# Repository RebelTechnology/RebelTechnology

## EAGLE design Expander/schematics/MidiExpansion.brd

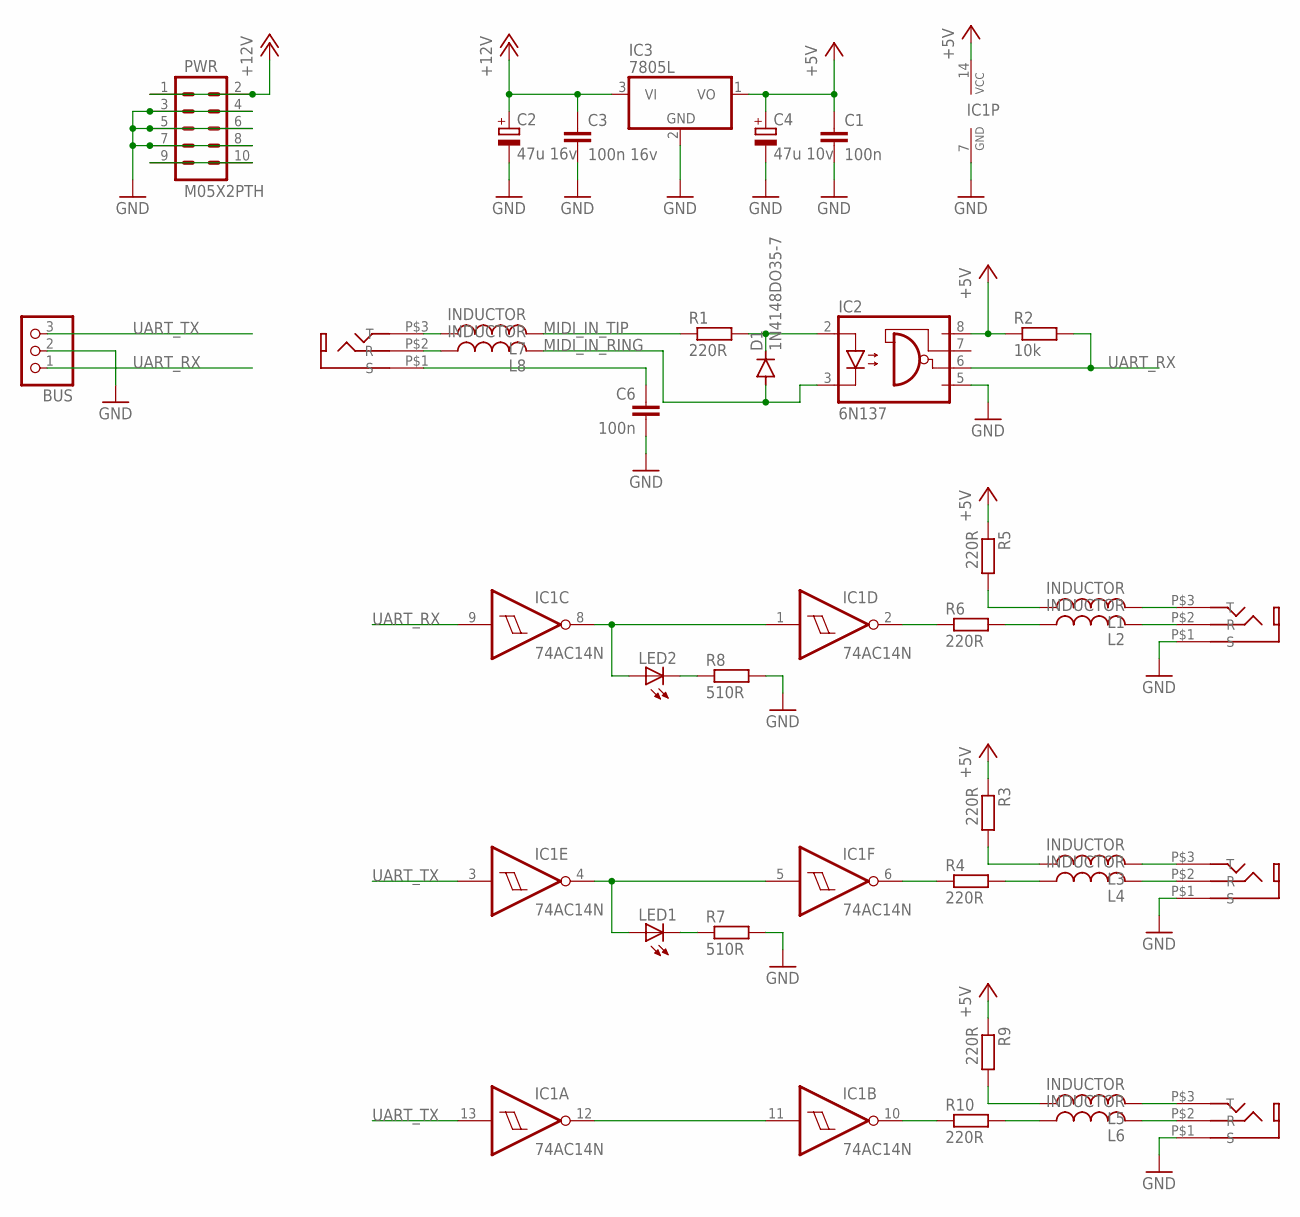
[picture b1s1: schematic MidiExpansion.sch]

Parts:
BUS: CON-JST-1X03PH-TH; JST-B3B-PH-KL
C1, C6: 100n; C050-024X044
C2: 47u 16v; E5-6
C3: 100n 16v; C050-024X044
C4: 47u 10v; E5-6
D1: 1N4148DO35-7; DO35-7
IC1: 74AC14N; DIL14
IC2: 6N137; DIL08
IC3: 7805L; TO92
L1, L2, L3, L4, L5, L6, L7, L8: INDUCTOR; 0603
LED1, LED2: LED3MM
MIDI_IN: THONKICONN_STEREO
MIDI_OUT, MIDI_OUT1: THONKICONN_STEREO
MIDI_THRU: THONKICONN_STEREO
PWR: M05X2PTH; AVR_ICSP
R1, R3, R4, R5, R6, R9, R10: 220R; 0204/7
R2: 10k; 0204/7
R7, R8: 510R; 0204/7

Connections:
+5V: C1.1, C4.+, IC1.14 (VCC), IC2.8 (VCC), IC3.1 (VO), R2.1, R3.1, R5.1, R9.1
+12V: C2.+, C3.1, IC3.3 (VI), PWR.1, PWR.2
GND: BUS.2, C1.2, C2.-, C3.2, C4.-, C6.2, IC1.7 (GND), IC2.5 (GND), IC3.2 (GND), MIDI_OUT.P$1 (S), MIDI_OUT1.P$1 (S), MIDI_THRU.P$1 (S), PWR.3, PWR.4, PWR.5, PWR.6, PWR.7, PWR.8, R7.2, R8.2
MIDI_IN_RING: D1.A, IC2.3 (C), L8.2
MIDI_IN_TIP: L7.2, R1.1
MIDI_OUT_TIP: L3.1, R3.2
MIDI_OUT_TIP1: L1.1, R5.2
MIDI_OUT_TIP2: L5.1, R9.2
unnamed: D1.C, IC2.2 (A), R1.2
unnamed: C6.1, MIDI_IN.P$1 (S)
unnamed: L2.2, MIDI_THRU.P$2 (R)
unnamed: IC1.6 (O), R4.1
unnamed: L4.2, MIDI_OUT.P$2 (R)
unnamed: IC1.4 (O), IC1.5 (I), LED1.A
unnamed: PWR.9, PWR.10
unnamed: IC1.2 (O), R6.1
unnamed: IC1.11 (I), IC1.12 (O)
unnamed: IC1.1 (I), IC1.8 (O), LED2.A
unnamed: L6.2, MIDI_OUT1.P$2 (R)
unnamed: IC1.10 (O), R10.1
unnamed: LED1.K (C), R7.1
unnamed: LED2.K (C), R8.1
unnamed: L1.2, MIDI_THRU.P$3 (T)
unnamed: L2.1, R6.2
unnamed: L3.2, MIDI_OUT.P$3 (T)
unnamed: L4.1, R4.2
unnamed: L5.2, MIDI_OUT1.P$3 (T)
unnamed: L6.1, R10.2
unnamed: L7.1, MIDI_IN.P$3 (T)
unnamed: L8.1, MIDI_IN.P$2 (R)
UART_RX: BUS.1, IC1.9 (I), IC2.6 (VO), R2.2
UART_TX: BUS.3, IC1.3 (I), IC1.13 (I)

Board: 2 copper layers, 35 parts (0 on the bottom side), 32 nets, no tracks yet.

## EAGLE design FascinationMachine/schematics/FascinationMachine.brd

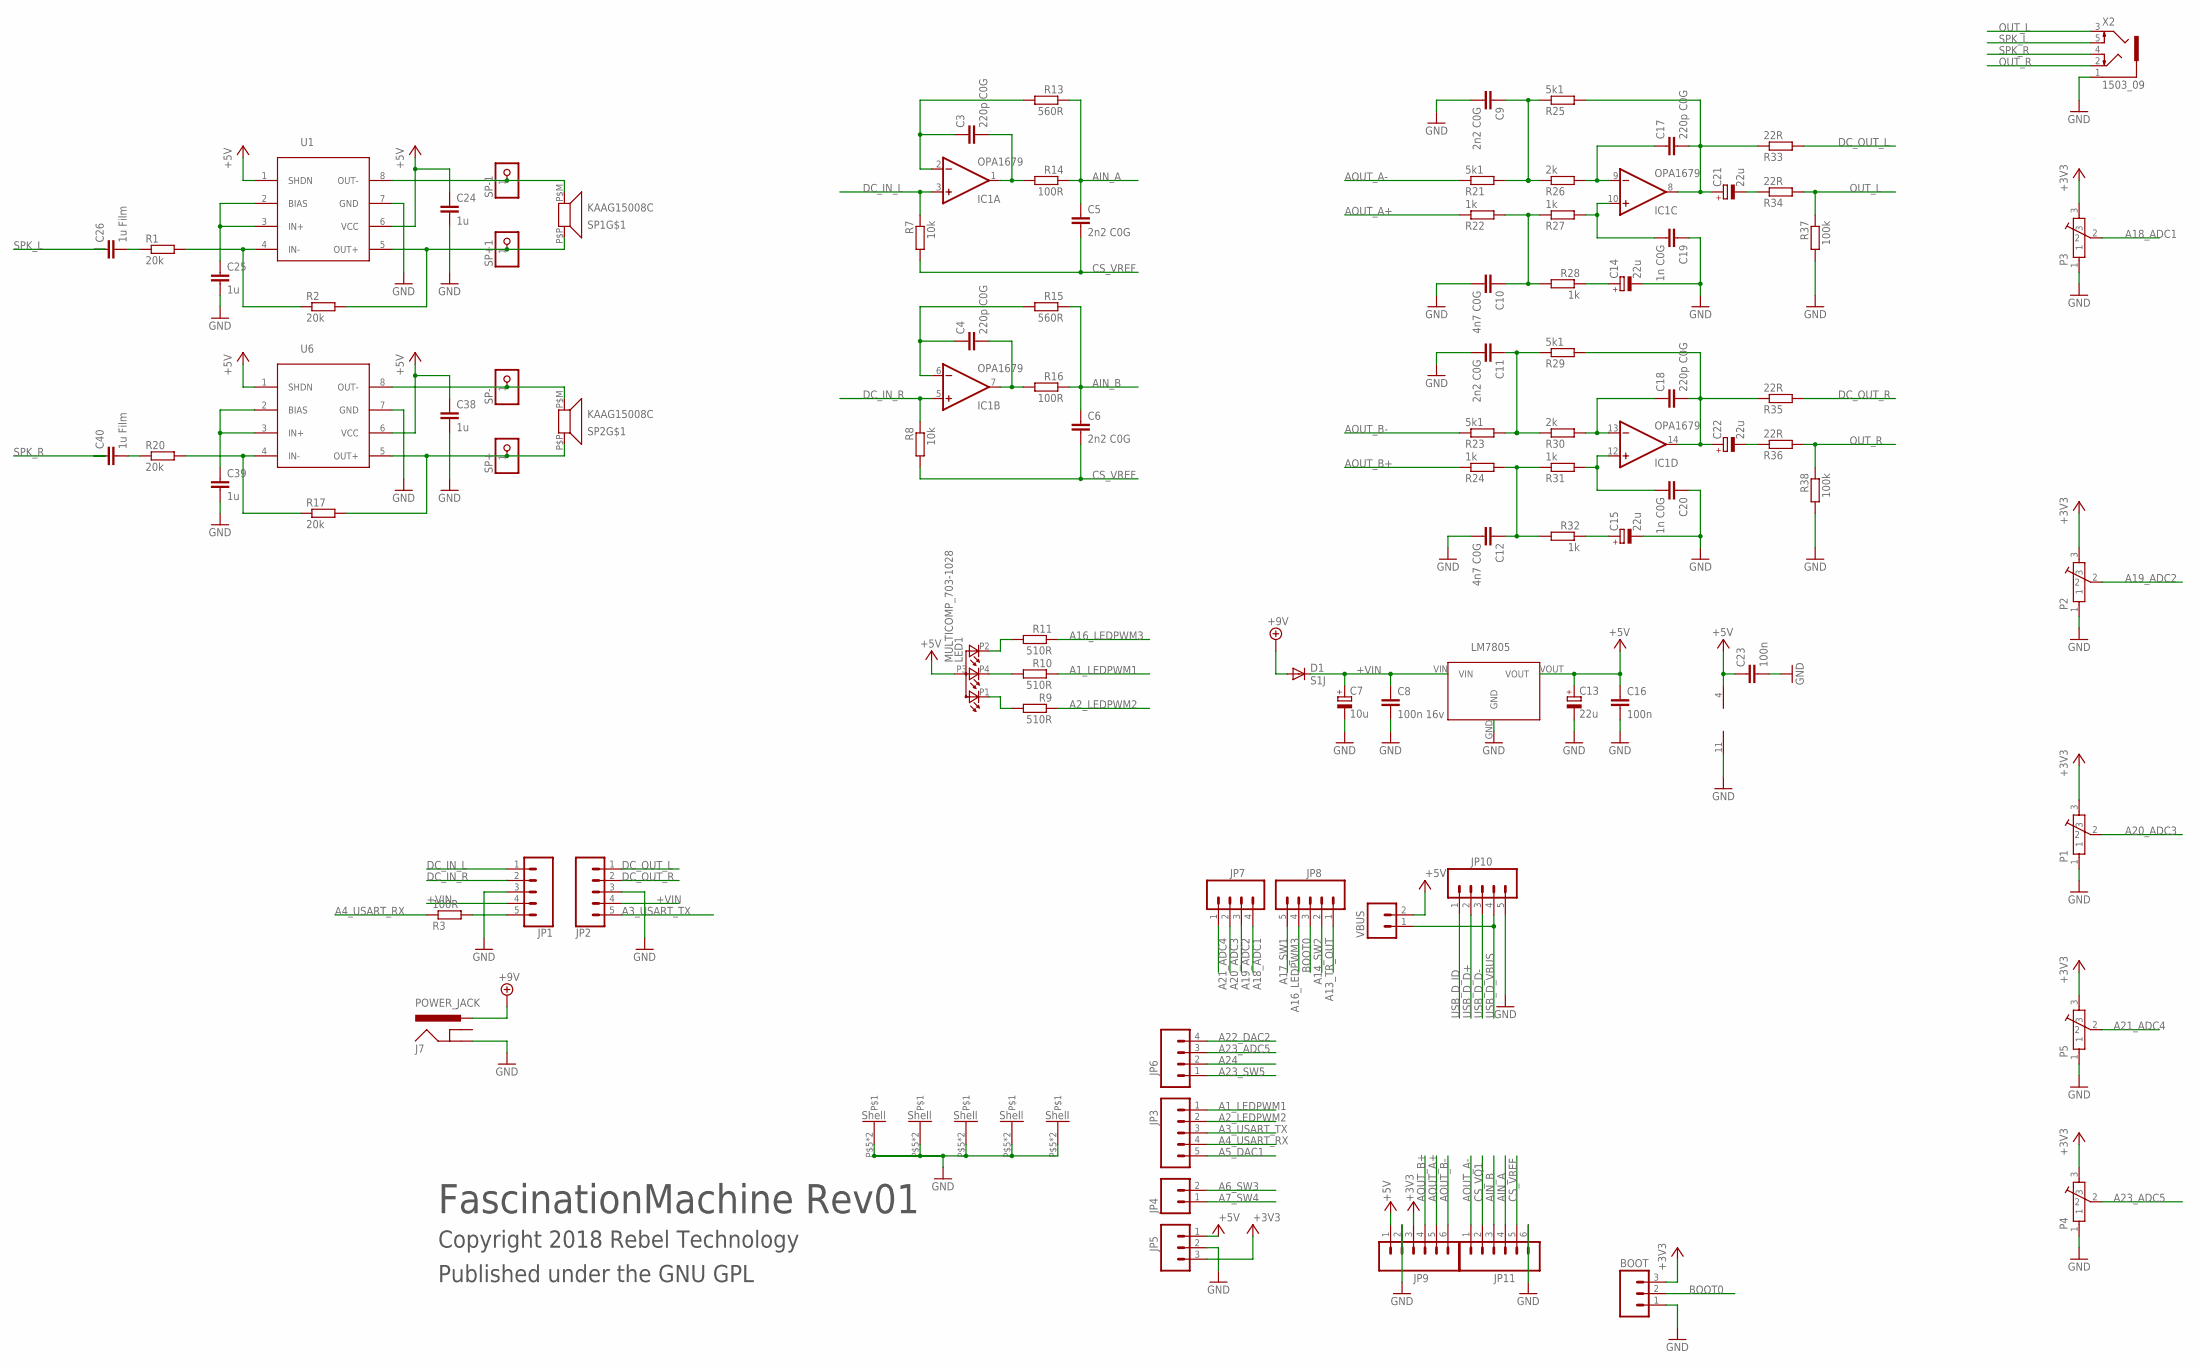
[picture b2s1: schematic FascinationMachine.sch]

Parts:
BOOT: M03PTH; 1X03
C3, C4, C17, C18: 220p C0G; C0603
C5, C6, C9, C11: 2n2 C0G; C0603
C7: 10u; 153CLV-0405
C8: 100n 16v; C0603
C10, C12: 4n7 C0G; C0603
C13, C14, C15, C21, C22: 22u; CPOL-5
C16, C23: 100n; C0603
C19, C20: 1n C0G; C0603
C24, C25, C38, C39: 1u; C0603
C26, C40: 1u Film; C1210
D1: S1J; SMA-DIODE
IC1: OPA1679; SO14
J7: POWER_JACK; DC_JACK_SLOT
JP1, JP2: CONN_05JST-VERT; JST-5-PTH-VERT
JP3, JP8, JP10: M05PTH; 1X05
JP4: M02PTH; 1X02
JP5: M03PTH; 1X03
JP6, JP7: M04PTH; 1X04
JP9, JP11: M06SIP; 1X06
LED1: MULTICOMP_703-1028; RGB-LED-703-1028
P1, P2, P3, P4, P5: POT-ALPS-RK09L1140
R1, R2, R17, R20: 20k; 0603
R3, R14, R16: 100R; 0603
R7, R8: 10k; 0603
R9, R10, R11: 510R; 0603
R13, R15: 560R; 0603
R21, R23, R25, R29: 5k1; 0603
R22, R24, R27, R28, R31, R32: 1k; 0603
R26, R30: 2k; 0603
R33, R34, R35, R36: 22R; 0603
R37, R38: 100k; 0603
SP1, SP2: KAAG15008C
SP+, SP+1: PINHD-1X1; 1X01
SP-, SP-1: PINHD-1X1; 1X01
U1, U6: MAX9716; UMAX8-THERMAL
U2: LM7805; REG_S9V11F5
VBUS: M02PTH; 1X02
X2: 1503_09

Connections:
+3V3: BOOT.3, JP5.3, JP9.3, P1.3, P2.3, P3.3, P4.3, P5.3
+5V: C13.+, C16.1, C23.1, C24.1, C38.1, IC1.4 (V+), JP5.1, JP9.1, LED1.P3 (A), U1.1 (SHDN), U1.6 (VCC), U2.VOUT, U6.1 (SHDN), U6.6 (VCC), VBUS.2
+9V: D1.A, J7.PWR
+VIN: C7.+, C8.1, D1.C, JP1.4, JP2.4, U2.VIN
A1_LEDPWM1: JP3.1, R10.1
A2_LEDPWM2: JP3.2, R9.1
A3_USART_TX: JP2.5, JP3.3
A4_USART_RX: JP3.4, R3.1
A5_DAC1: JP3.5
A6_SW3: JP4.2
A7_SW4: JP4.1
A13_TR_OUT: JP8.1
A14_SW2: JP8.2
A16_LEDPWM3: JP8.4, R11.1
A17_SW1: JP8.5
A18_ADC1: JP7.4, P3.2
A19_ADC2: JP7.3, P2.2
A20_ADC3: JP7.2, P1.2
A21_ADC4: JP7.1, P5.2
A22_DAC2: JP6.4
A23_ADC5: JP6.3, P4.2
A23_SW5: JP6.1
A24: JP6.2
AIN_A: C5.1, JP11.4, R13.1, R14.1
AIN_B: C6.1, JP11.3, R15.1, R16.1
AOUT_A+: JP9.5, R22.1
AOUT_A-: JP11.1, R21.1
AOUT_B+: JP9.4, R24.1
AOUT_B-: JP9.6, R23.1
BOOT0: BOOT.2, JP8.3
CS_VQ1: JP11.2
CS_VREF: C5.2, C6.2, JP11.5, R7.2, R8.2
DC_IN_L: IC1.3 (+IN), JP1.1, R7.1
DC_IN_R: IC1.5 (+IN), JP1.2, R8.1
DC_OUT_L: JP2.1, R33.2
DC_OUT_R: JP2.2, R35.2
GND: BOOT.1, C7.-, C8.2, C9.2, C10.2, C11.2, C12.2, C13.-, C14.-, C15.-, C16.2, C19.1, C20.1, C23.2, C24.2, C25.2, C38.2, C39.2, IC1.11 (V-), J7.GND, JP1.3, JP2.3, JP5.2, JP9.2, JP10.5, JP11.6, P1.1, P1.P$5, P1.P$6, P2.1, P2.P$5, P2.P$6, P3.1, P3.P$5, P3.P$6, P4.1, P4.P$5, P4.P$6, P5.1, P5.P$5, P5.P$6, R37.2, R38.2, U1.7 (GND), U2.GND, U6.7 (GND), X2.1
unnamed: JP1.5, R3.2
unnamed: R2.2, SP1.P$P (1), SP+1.1, U1.5 (OUT+)
unnamed: C3.1, IC1.2 (-IN), R13.2
unnamed: C4.2, IC1.7 (OUT), R16.2
unnamed: C4.1, IC1.6 (-IN), R15.2
unnamed: C3.2, IC1.1 (OUT), R14.2
unnamed: C17.1, IC1.9 (-IN), R26.2
unnamed: C15.+, R32.1
unnamed: C21.-, R34.1
unnamed: C14.+, R28.1
unnamed: C19.2, IC1.10 (+IN), R27.2
unnamed: C18.2, C22.+, IC1.14 (OUT), R29.2, R35.1
unnamed: C22.-, R36.1
unnamed: LED1.P2 (CGREEN), R11.2
unnamed: C10.1, R22.2, R27.1, R28.2
unnamed: LED1.P1 (CRED), R9.2
unnamed: LED1.P4 (CBLUE), R10.2
unnamed: SP1.P$M (2), SP-1.1, U1.8 (OUT-)
unnamed: C25.1, U1.2 (BIAS), U1.3 (IN+)
unnamed: R1.2, R2.1, U1.4 (IN-)
unnamed: C26.2, R1.1
unnamed: C11.1, R23.2, R29.1, R30.1
unnamed: C18.1, IC1.13 (-IN), R30.2
unnamed: C20.2, IC1.12 (+IN), R31.2
unnamed: C12.1, R24.2, R31.1, R32.2
unnamed: C17.2, C21.+, IC1.8 (OUT), R25.2, R33.1
unnamed: C9.1, R21.2, R25.1, R26.1
unnamed: R17.2, SP2.P$P (1), SP+.1, U6.5 (OUT+)
unnamed: SP2.P$M (2), SP-.1, U6.8 (OUT-)
unnamed: C39.1, U6.2 (BIAS), U6.3 (IN+)
unnamed: R17.1, R20.2, U6.4 (IN-)
unnamed: C40.2, R20.1
OUT_L: R34.2, R37.1, X2.3
OUT_R: R36.2, R38.1, X2.2
SPK_L: C26.1, X2.5
SPK_R: C40.1, X2.4
USB_D_D+: JP10.2
USB_D_D-: JP10.3
USB_D_ID: JP10.1
USB_D_VBUS: JP10.4, VBUS.1

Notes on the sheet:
FascinationMachine Rev01
Copyright 2018 Rebel Technology
Published under the GNU GPL

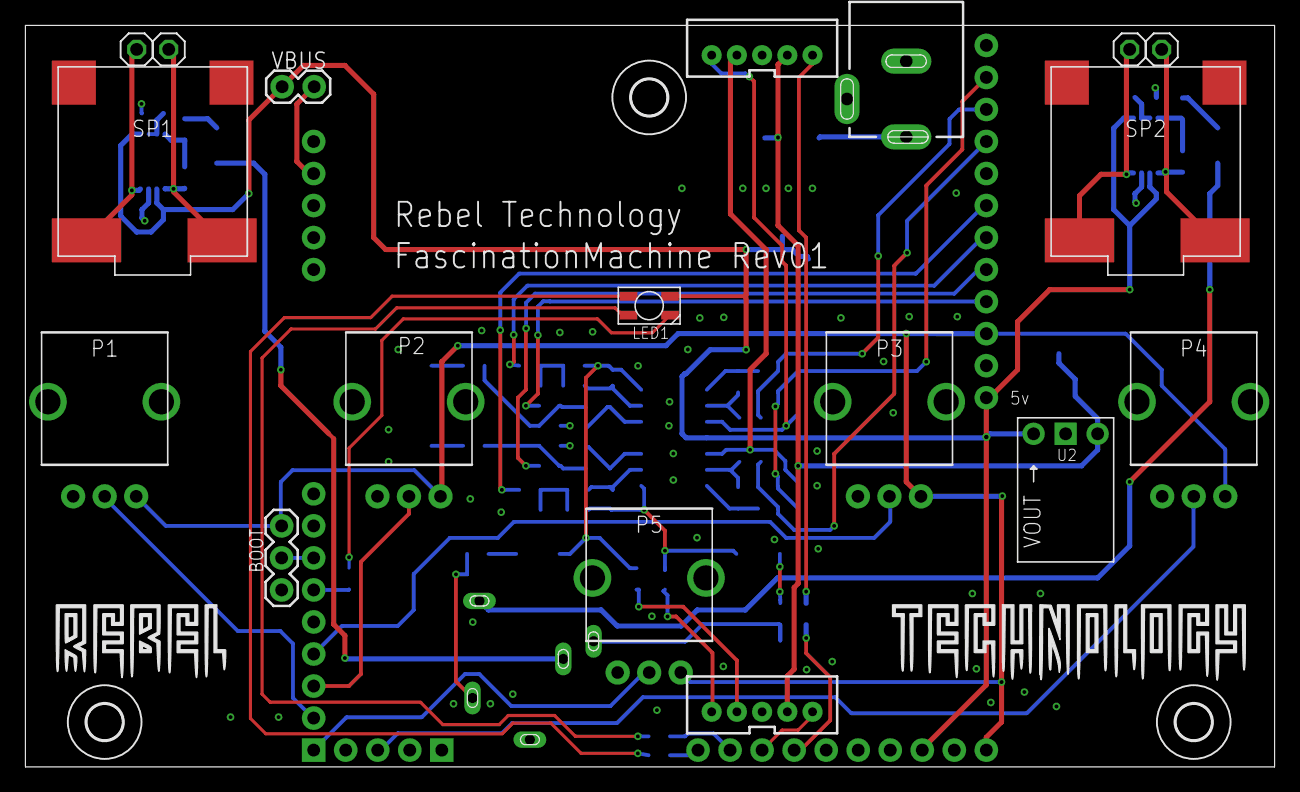
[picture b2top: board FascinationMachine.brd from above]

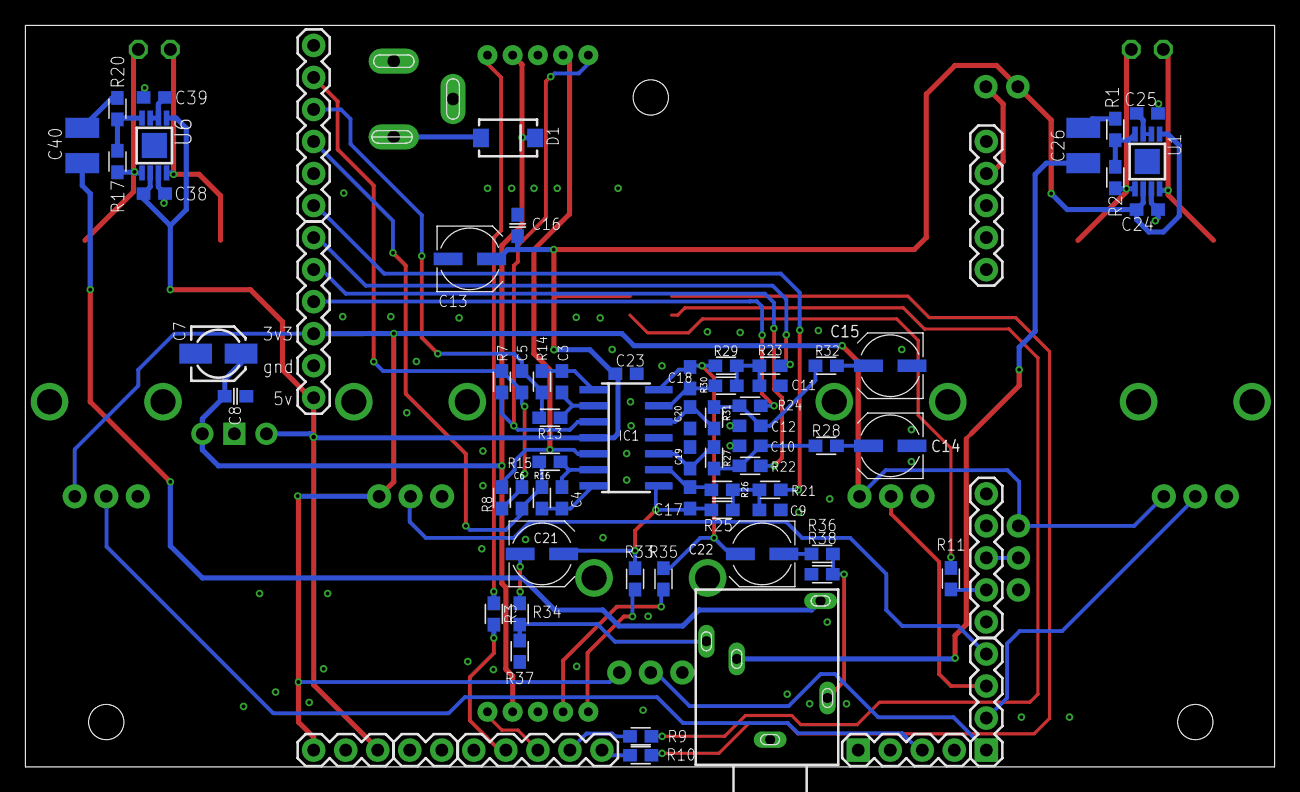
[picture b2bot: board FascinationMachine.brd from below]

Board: 2 copper layers, 99.1 x 58.8 mm, 94 parts (73 on the bottom side), 64 nets.

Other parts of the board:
U$1, U$2, U$3: 2,8

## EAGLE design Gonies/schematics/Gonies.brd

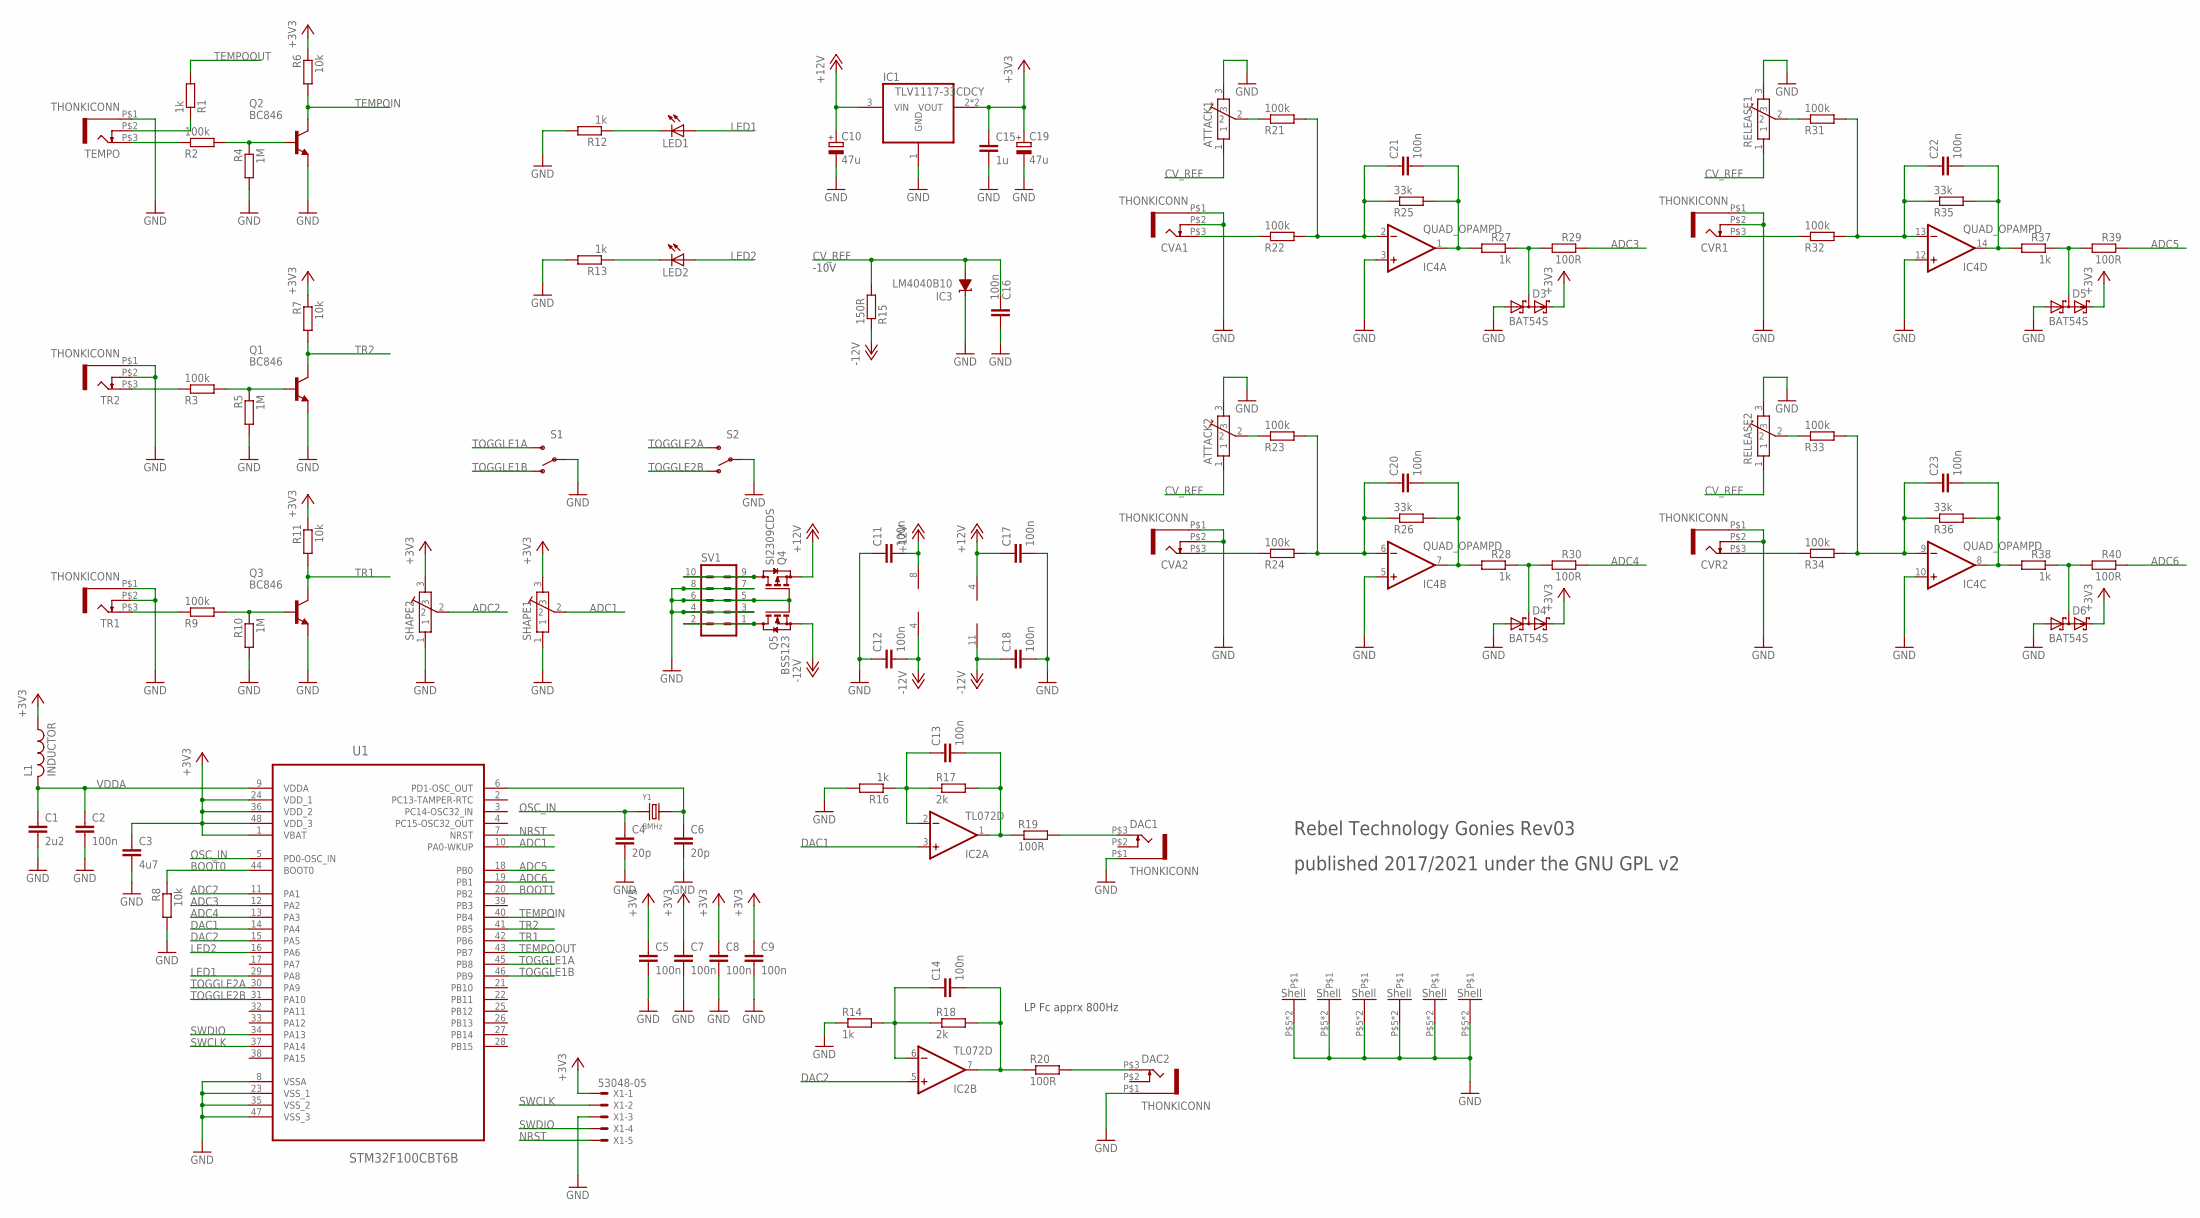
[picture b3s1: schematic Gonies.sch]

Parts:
ATTACK1, ATTACK2: POT-ALPS-RK09L1140
C1: 2u2; C0603
C2, C5, C7, C8, C9, C11, C12, C13, C14, C16, C17, C18, C20, C21, C22, C23: 100n; C0603
C3: 4u7; C0603
C4, C6: 20p; C0603
C10, C19: 47u; CPOL-5; FARNELL 882-3014
C15: 1u; C0603
CVA1, CVA2: THONKICONN
CVR1, CVR2: THONKICONN
D3, D4, D5, D6: BAT54S; SOT23
DAC1, DAC2: THONKICONN
IC1: TLV1117-33CDCY; SOT223; FARNELL 149-4942
IC2: TL072D; SO08
IC3: LM4040B10; DBZ_R-PDSO-G3
IC4: QUAD_OPAMPD; SO14
L1: INDUCTOR; 0603
LED1, LED2: LED3MM
Q1, Q2, Q3: BC846; SOT23
Q4: SI2309CDS; SOT23
Q5: BSS123; SOT23
R1, R12, R13, R14, R16, R27, R28, R37, R38: 1k; 0603
R2, R3, R9, R21, R22, R23, R24, R31, R32, R33, R34: 100k; 0603
R4, R5, R10: 1M; 0603
R6, R7, R8, R11: 10k; 0603
R15: 150R; 0603
R17, R18: 2k; 0603
R19, R20, R29, R30, R39, R40: 100R; 0603
R25, R26, R35, R36: 33k; 0603
RELEASE1, RELEASE2: POT-ALPS-RK09L1140
S1, S2: SWITCH-SPST; SWITCH-SPDT-SALECOM-T8014
SHAPE1, SHAPE2: POT-ALPS-RK09L1140
SV1: MA05-2
TEMPO: THONKICONN
TR1, TR2: THONKICONN
U1: STM32F100CBT6B; QFP50P900X900X160-48N
X1: 53048-05
Y1: 8MHz; X2-SMD-5.0X3.2X1.3MM

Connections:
+3V3: C3.1, C5.1, C7.1, C8.1, C9.1, C15.1, C19.+, D3.2 (C2), D4.2 (C2), D5.2 (C2), D6.2 (C2), IC1.2 (VOUT), IC1.4 (VOUT), L1.1, R6.1, R7.1, R11.1, SHAPE1.3, SHAPE2.3, U1.1 (VBAT), U1.24 (VDD_1), U1.36 (VDD_2), U1.48 (VDD_3), X1.1
+12V: C10.+, C11.2, C17.1, IC1.3 (VIN), IC2.8 (V+), IC4.4 (V+), Q4.2 (S)
-12V: C12.2, C18.1, IC2.4 (V-), IC4.11 (V-), Q5.2 (S), R15.1
ADC1: SHAPE1.2, U1.10 (PA0-WKUP)
ADC2: SHAPE2.2, U1.11 (PA1)
ADC3: R29.1, U1.12 (PA2)
ADC4: R30.1, U1.13 (PA3)
ADC5: R39.1, U1.18 (PB0)
ADC6: R40.1, U1.19 (PB1)
BOOT0: R8.1, U1.44 (BOOT0)
BOOT1: U1.20 (PB2)
CV_REF: ATTACK1.1, ATTACK2.1, C16.1, IC3.2 (A), R15.2, RELEASE1.1, RELEASE2.1
DAC1: IC2.3 (+IN), U1.14 (PA4)
DAC2: IC2.5 (+IN), U1.15 (PA5)
GND: ATTACK1.3, ATTACK1.P$5, ATTACK1.P$6, ATTACK2.3, ATTACK2.P$5, ATTACK2.P$6, C1.2, C2.2, C3.2, C4.2, C5.2, C6.2, C7.2, C8.2, C9.2, C10.-, C11.1, C12.1, C15.2, C16.2, C17.2, C18.2, C19.-, CVA1.P$1 (5), CVA1.P$2 (4), CVA2.P$1 (5), CVA2.P$2 (4), CVR1.P$1 (5), CVR1.P$2 (4), CVR2.P$1 (5), CVR2.P$2 (4), D3.1 (A1), D4.1 (A1), D5.1 (A1), D6.1 (A1), DAC1.P$1 (5), DAC2.P$1 (5), IC1.1 (GND), IC3.1 (C), IC4.3 (+IN), IC4.5 (+IN), IC4.10 (+IN), IC4.12 (+IN), Q1.2 (E), Q2.2 (E), Q3.2 (E), Q4.1 (G), Q5.1 (G), R4.2, R5.2, R8.2, R10.2, R12.2, R13.2, R14.1, R16.2, RELEASE1.3, RELEASE1.P$5, RELEASE1.P$6, RELEASE2.3, RELEASE2.P$5, RELEASE2.P$6, S1.2, S2.2, SHAPE1.1, SHAPE1.P$5, SHAPE1.P$6, SHAPE2.1, SHAPE2.P$5, SHAPE2.P$6, SV1.3, SV1.4, SV1.5, SV1.6, SV1.7, SV1.8, TEMPO.P$1 (5), TR1.P$1 (5), TR1.P$2 (4), TR2.P$1 (5), TR2.P$2 (4), U1.8 (VSSA), U1.23 (VSS_1), U1.35 (VSS_2), U1.47 (VSS_3), X1.3
LED1: LED1.A, U1.29 (PA8)
LED2: LED2.A, U1.16 (PA6)
unnamed: C6.1, U1.6 (PD1-OSC_OUT), Y1.2
unnamed: LED2.K (C), R13.1
unnamed: C14.2, IC2.7 (OUT), R18.2, R20.1
unnamed: C14.1, IC2.6 (-IN), R14.2, R18.1
unnamed: Q4.3 (D), SV1.9, SV1.10
unnamed: C13.2, IC2.1 (OUT), R17.2, R19.1
unnamed: LED1.K (C), R12.1
unnamed: Q1.1 (B), R3.2, R5.1
unnamed: Q2.1 (B), R2.2, R4.1
unnamed: R2.1, TEMPO.P$3 (3)
unnamed: C13.1, IC2.2 (-IN), R16.1, R17.1
unnamed: R3.1, TR2.P$3 (3)
unnamed: Q5.3 (D), SV1.1, SV1.2
unnamed: R1.1, TEMPO.P$2 (4)
unnamed: CVA1.P$3 (3), R22.1
unnamed: C21.1, IC4.2 (-IN), R21.2, R22.2, R25.1
unnamed: ATTACK1.2, R21.1
unnamed: C21.2, IC4.1 (OUT), R25.2, R27.2
unnamed: R9.1, TR1.P$3 (3)
unnamed: D3.3 (C1A2), R27.1, R29.2
unnamed: CVA2.P$3 (3), R24.1
unnamed: C20.1, IC4.6 (-IN), R23.2, R24.2, R26.1
unnamed: Q3.1 (B), R9.2, R10.1
unnamed: ATTACK2.2, R23.1
unnamed: C20.2, IC4.7 (OUT), R26.2, R28.2
unnamed: DAC1.P$3 (3), R19.2
unnamed: DAC2.P$3 (3), R20.2
unnamed: D4.3 (C1A2), R28.1, R30.2
unnamed: CVR1.P$3 (3), R32.1
unnamed: C22.1, IC4.13 (-IN), R31.2, R32.2, R35.1
unnamed: R31.1, RELEASE1.2
unnamed: C22.2, IC4.14 (OUT), R35.2, R37.2
unnamed: D5.3 (C1A2), R37.1, R39.2
unnamed: CVR2.P$3 (3), R34.1
unnamed: C23.1, IC4.9 (-IN), R33.2, R34.2, R36.1
unnamed: R33.1, RELEASE2.2
unnamed: C23.2, IC4.8 (OUT), R36.2, R38.2
unnamed: D6.3 (C1A2), R38.1, R40.2
NRST: U1.7 (NRST), X1.5
OSC_IN: C4.1, U1.5 (PD0-OSC_IN), Y1.1
SWCLK: U1.37 (PA14), X1.2
SWDIO: U1.34 (PA13), X1.4
TEMPOIN: Q2.3 (C), R6.2, U1.40 (PB4)
TEMPOOUT: R1.2, U1.43 (PB7)
TOGGLE1A: S1.3 (S), U1.45 (PB8)
TOGGLE1B: S1.1 (O), U1.46 (PB9)
TOGGLE2A: S2.3 (S), U1.30 (PA9)
TOGGLE2B: S2.1 (O), U1.31 (PA10)
TR1: Q3.3 (C), R11.2, U1.42 (PB6)
TR2: Q1.3 (C), R7.2, U1.41 (PB5)
VDDA: C1.1, C2.1, L1.2, U1.9 (VDDA)

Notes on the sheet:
Rebel Technology Gonies Rev03
published 2017/2021 under the GNU GPL v2
LP Fc apprx 800Hz
-10V

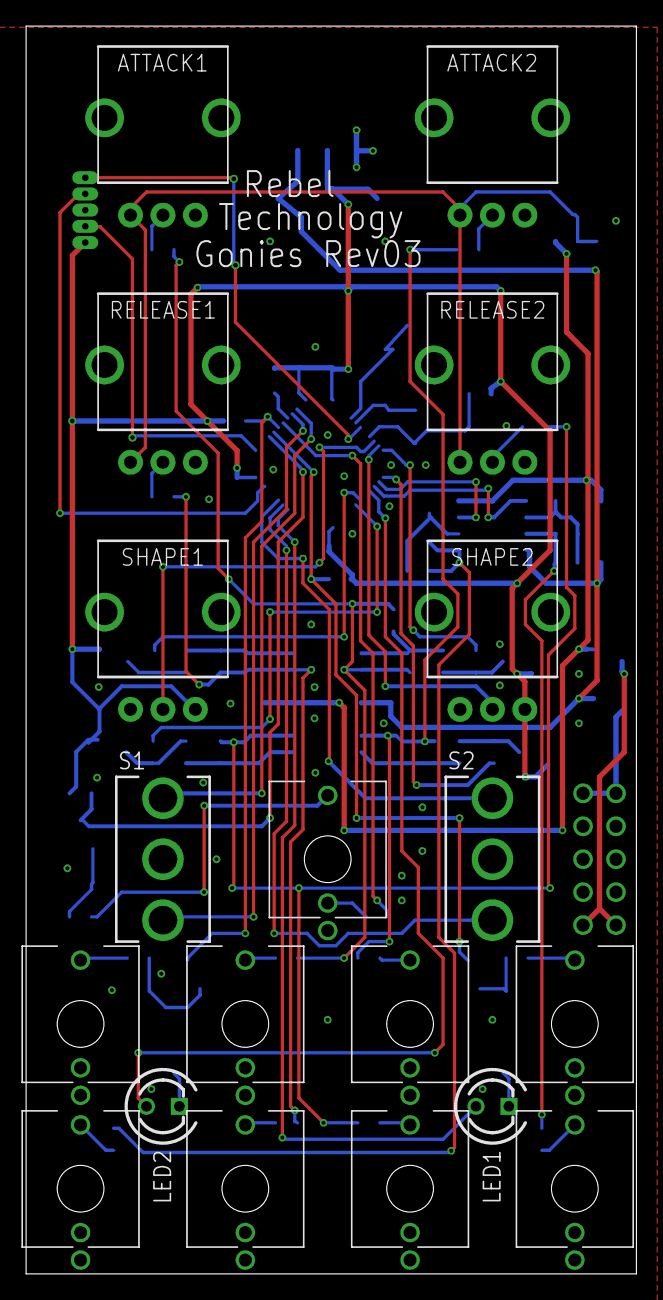
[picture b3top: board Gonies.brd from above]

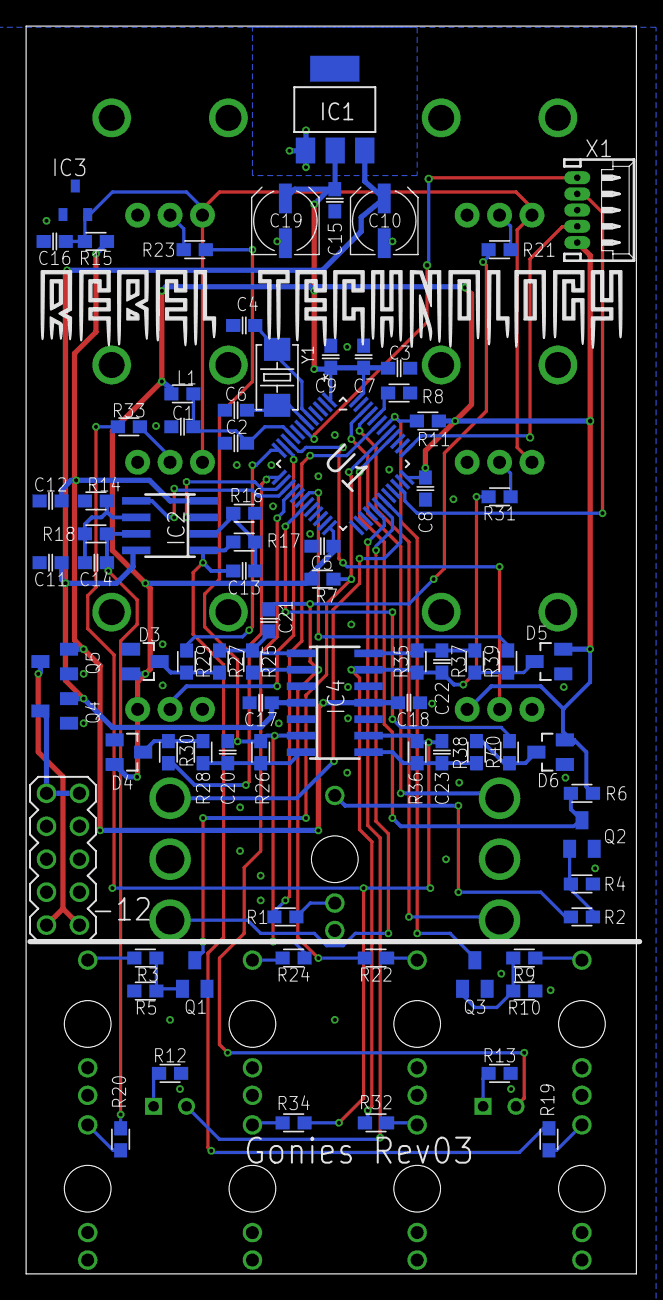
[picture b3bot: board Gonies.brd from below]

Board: 2 copper layers, 47.0 x 96.2 mm, 100 parts (81 on the bottom side), 67 nets.

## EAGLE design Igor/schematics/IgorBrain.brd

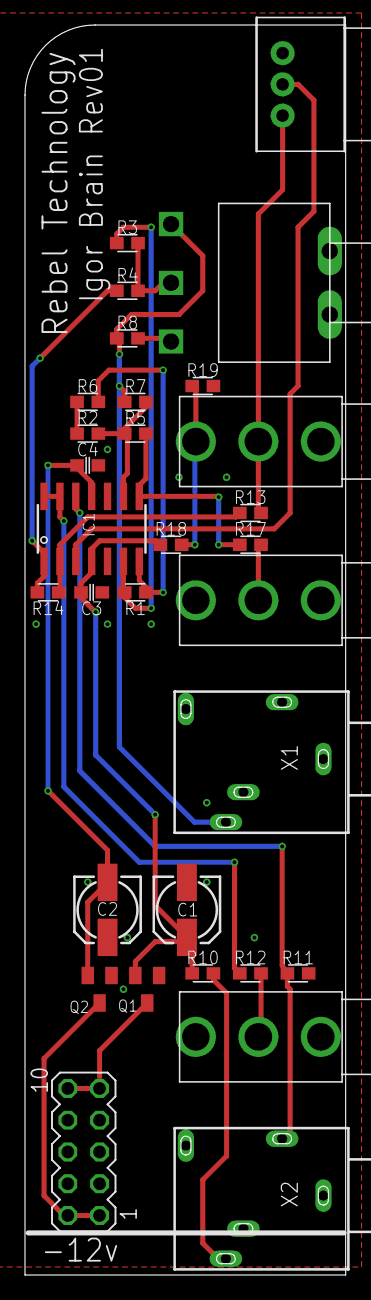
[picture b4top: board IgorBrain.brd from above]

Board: 2 copper layers, 25.7 x 100.0 mm, 31 parts (0 on the bottom side), 23 nets.

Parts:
C1, C2: 10u; 153CLV-0505
C3, C4: 100n; C0603
IC1: QUAD_OPAMPD; SO14
IN1: JACK-UJ-3502-R; UJ-3502-R
OUT1, OUT2: JACK-UJ-3502-R; UJ-3502-R
P1: 10k lin; POT-BOURNS-PTD901
Q1: SI2309CDS; SOT23
Q2: BSS123; SOT23
R1, R2, R3, R7, R18, R19: 10k; 0603
R4, R10, R12, R17: 1k; 0603
R5, R13, R14: 22k; 0603
R6, R8: 5k1; 0603
R11: 100k; 0603
SV1: MA05-2
SW1: SWITCH-TOGGLE; SWITCH-SPDT-SALECOM-T8020
X1, X2: 1503_09

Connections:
+12V: C1.+, C3.1, IC1.4, Q1.2, R10.1, R18.1
-12V: C2.-, C4.1, IC1.11, Q2.2
GND: C1.-, C2.+, C3.2, C4.2, IC1.5, IC1.10, IN1.P$3, OUT1.P$3, OUT2.P$3, P1.3, Q1.1, Q2.1, R11.2, R19.2, SV1.3, SV1.4, SV1.5, SV1.6, SV1.7, SV1.8, X1.1, X1.2, X2.1
unnamed: Q2.3, SV1.1, SV1.2
unnamed: R7.2, R8.1, SW1.3, X1.3
unnamed: R3.2, R4.2, SW1.2
unnamed: IC1.8, R5.1, R17.1
unnamed: IC1.7, R1.1, R6.2
unnamed: R2.2, R6.1
unnamed: R8.2, SW1.1
unnamed: IN1.P$1, P1.1, R13.1
unnamed: IC1.2, R13.2, R14.1
unnamed: IC1.1, R4.1, R14.2
unnamed: IC1.9, R2.1, R5.2, R7.1
unnamed: R10.2, X2.3
unnamed: IC1.13, IC1.14, R12.1
unnamed: Q1.3, SV1.9, SV1.10
unnamed: OUT2.P$1, R12.2
unnamed: IC1.12, R11.1, X2.2
unnamed: IC1.3, P1.2
unnamed: OUT1.P$1, R17.2
unnamed: IN1.P$2, R18.2, R19.1
unnamed: IC1.6, R1.2, R3.1

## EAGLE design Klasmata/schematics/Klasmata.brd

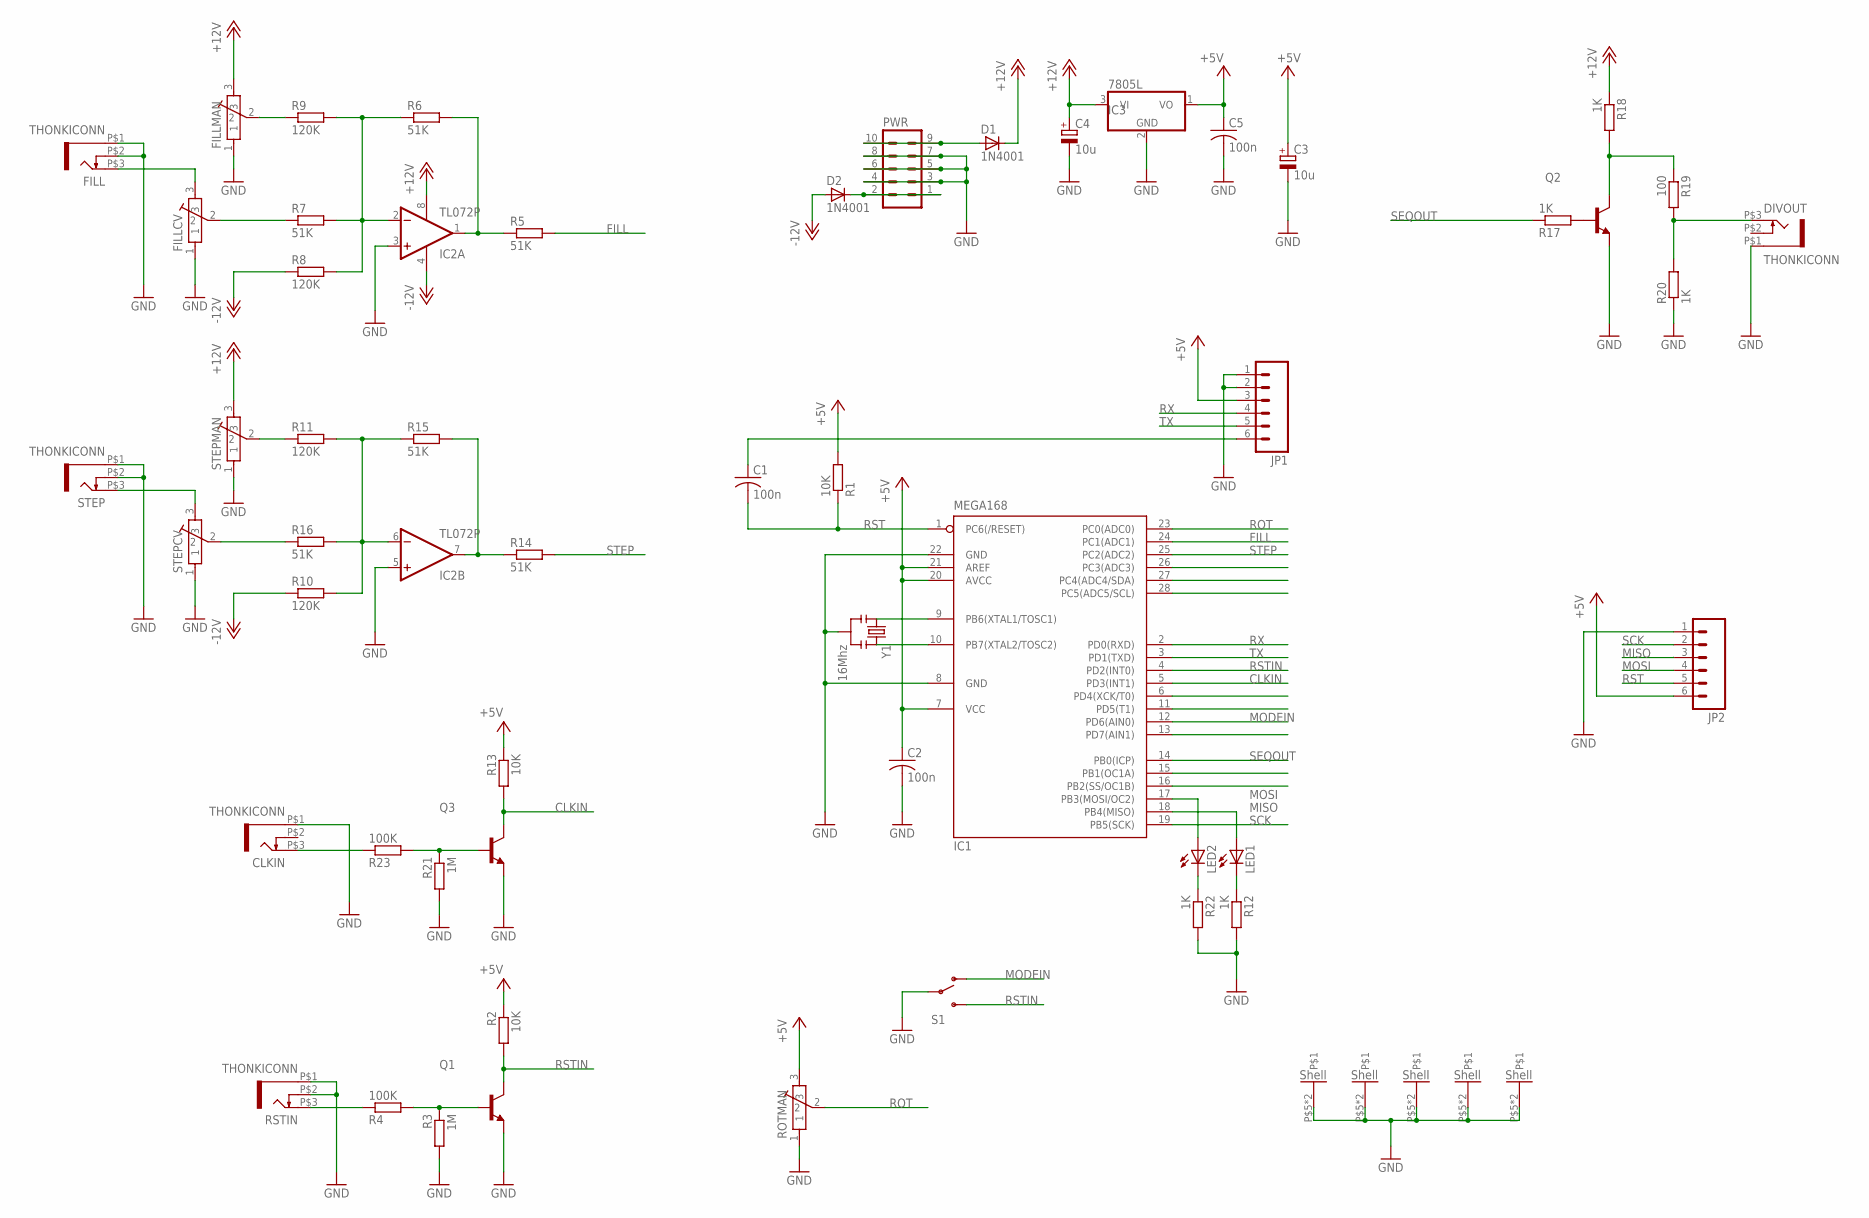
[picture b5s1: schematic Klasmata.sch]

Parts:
C1, C2, C5: 100n; C050-024X044
C3: 10u; E2,5-6
C4: 10u; E5-6
CLKIN: THONKICONN
D1, D2: 1N4001; DIODE-1N4001
DIVOUT: THONKICONN
FILL: THONKICONN
FILLCV: POT-ALPS-RK09L1140
FILLMAN: POT-ALPS-RK09L1140
IC1: MEGA168; DIL28-3
IC2: TL072P; DIL08
IC3: 7805L; TO92
JP1, JP2: M06SIP; 1X06
LED1, LED2: LED3MM
PWR: MA05-2
Q1, Q2, Q3: 2N3904-NPN-TO92-EBC; TO92-EBC
R1, R2, R13: 10K; 0204/7
R3, R21: 1M; 0204/7
R4, R23: 100K; 0204/7
R5, R6, R7, R14, R15, R16: 51K; 0204/7
R8, R9, R10, R11: 120K; 0204/7
R12, R17, R18, R20, R22: 1K; 0204/7
R19: 100; 0204/7
ROTMAN: POT-ALPS-RK09L1140
RSTIN: THONKICONN
S1: SWITCH-SPST; SWITCH-SPDT-SALECOM-T8014
STEP: THONKICONN
STEPCV: POT-ALPS-RK09L1140
STEPMAN: POT-ALPS-RK09L1140
Y1: 16Mhz; RESONATOR-PTH

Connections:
+5V: C2.1, C3.+, C5.1, IC1.7 (VCC), IC1.20 (AVCC), IC1.21 (AREF), IC3.1 (VO), JP1.3, JP2.6, R1.2, R2.1, R13.1, ROTMAN.3
+12V: C4.+, D1.C, FILLMAN.3, IC2.8 (V+), IC3.3 (VI), R18.1, STEPMAN.3
-12V: D2.A, IC2.4 (V-), R8.1, R10.1
ALT: IC1.11 (PD5(T1))
CLKIN: IC1.5 (PD3(INT1)), Q3.C, R13.2
CMBOUT: IC1.16 (PB2(SS/OC1B))
DELOUT: IC1.15 (PB1(OC1A))
FILL: IC1.24 (PC1(ADC1)), R5.2
GND: C2.2, C3.-, C4.-, C5.2, CLKIN.P$1 (5), DIVOUT.P$1 (5), FILL.P$1 (5), FILL.P$2 (4), FILLCV.1, FILLCV.P$5, FILLCV.P$6, FILLMAN.1, FILLMAN.P$5, FILLMAN.P$6, IC1.8 (GND), IC1.22 (GND), IC2.3 (+IN), IC2.5 (+IN), IC3.2 (GND), JP1.1, JP1.2, JP2.1, PWR.3, PWR.4, PWR.5, PWR.6, PWR.7, PWR.8, Q1.E, Q2.E, Q3.E, R3.2, R12.2, R20.1, R21.2, R22.2, ROTMAN.1, ROTMAN.P$5, ROTMAN.P$6, RSTIN.P$1 (5), RSTIN.P$2 (4), S1.2, STEP.P$1 (5), STEP.P$2 (4), STEPCV.1, STEPCV.P$5, STEPCV.P$6, STEPMAN.1, STEPMAN.P$5, STEPMAN.P$6, Y1.2
MISO: IC1.18 (PB4(MISO)), JP2.3, LED1.A
MODEB: IC1.13 (PD7(AIN1))
MODEIN: IC1.12 (PD6(AIN0)), S1.1 (O)
MOSI: IC1.17 (PB3(MOSI/OC2)), JP2.4, LED2.A
unnamed: FILL.P$3 (3), FILLCV.3
unnamed: IC2.2 (-IN), R6.1, R7.2, R8.2, R9.2
unnamed: FILLMAN.2, R9.1
unnamed: IC2.1 (OUT), R5.1, R6.2
unnamed: FILLCV.2, R7.1
unnamed: D1.A, PWR.9, PWR.10
unnamed: IC2.6 (-IN), R10.2, R11.2, R15.1, R16.2
unnamed: R11.1, STEPMAN.2
unnamed: IC2.7 (OUT), R14.1, R15.2
unnamed: R16.1, STEPCV.2
unnamed: STEP.P$3 (3), STEPCV.3
unnamed: IC1.9 (PB6(XTAL1/TOSC1)), Y1.1
unnamed: IC1.10 (PB7(XTAL2/TOSC2)), Y1.3
unnamed: LED2.K (C), R22.1
unnamed: LED1.K (C), R12.1
unnamed: Q3.B, R21.1, R23.2
unnamed: CLKIN.P$3 (3), R23.1
unnamed: C1.1, JP1.6
unnamed: Q1.B, R3.1, R4.2
unnamed: Q2.B, R17.2
unnamed: DIVOUT.P$3 (3), R19.2, R20.2
unnamed: Q2.C, R18.2, R19.1
unnamed: R4.1, RSTIN.P$3 (3)
unnamed: D2.C, PWR.1, PWR.2
ROT: IC1.23 (PC0(ADC0)), ROTMAN.2
RST: C1.2, IC1.1 (PC6(/RESET)), JP2.5, R1.1
RSTIN: IC1.4 (PD2(INT0)), Q1.C, R2.2, S1.3 (S)
RX: IC1.2 (PD0(RXD)), JP1.4
SCK: IC1.19 (PB5(SCK)), JP2.2
SEQOUT: IC1.14 (PB0(ICP)), R17.1
STEP: IC1.25 (PC2(ADC2)), R14.2
TRIG: IC1.6 (PD4(XCK/T0))
TX: IC1.3 (PD1(TXD)), JP1.5

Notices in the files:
parts and their libraries:
SparkFun: Licensing: CC v3.0 Share-Alike You are welcome to use this library for commercial purposes.
SparkFun-Connectors: Licensing: Creative Commons ShareAlike 4.0 International - https://creativecommons.org/licenses/by-sa/4.0
